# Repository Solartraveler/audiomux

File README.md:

# Audiomux
This project provides a box for switching 4 stereo audio inputs to 4 outputs. Any combination of inputs to outputs can be selected at the same time.
Signal dissortion is minimized by using reed relays.
Moreover, this provides galvanic isolation from the control circuit and if the input source can drive a headphone, it will work on the output of the mux too.
Allowing control by two USB ports, this can be easily used for a homeoffice + private PC setup. Controlling with an infrared remote control is possible too.
The power supply can come from one of the USB ports or one of two external 6-12V power supplies.
For each power supply source, one predefined input to output mux configuration can be saved in the internal flash.

## Host program
A host program for communicating is provided.
Written in python, it is platform independent. Linux was tested.
Setting output 1 to input 2, call the program as following:

./audiomux-control.py 1 2

Call without parameters to get the current setup. Call

./audiomux-control.py state

to get all predefined configurations for IR remote control codes and Vcc inputs.
The input voltages and internal temperature are printed too.

A debian package can be generated.

## Compiling and uploading

There is no additional programming hardware needed.

With apt install the packages gcc-arm-none-eabi, make, dfu-util and python3-usb.

Next, call make

Then close J4 and call ./dfu-upload.sh

Later, leave J4 open to directly start the flashed program. You have to repeat this for both PCBs.

## Debugging

You can add a serial port with 3.3V level to J11 and see some debug messages when using 19200baud.

Debugging with SWD should be possible too, but this was not tested.

## Bugs

Maybe the biggest bug in the is the counterintuitive ordering of the in and outputs...

The soldering bridges would allow switching input (3 and 4) and/or (1 and 2).

## Libraries used and licenses

The software uses several open source libraries with different licenses.

The HAL library from ST is published under the BSD 3-Clause license.

Some CMSIS header files are published under the Apache 2.0 license.

The [IRMP](https://www.mikrocontroller.net/articles/IRMP_-_english) project is published under GPL 2.0 or later.

[Libusb_stm32](https://github.com/dmitrystu/libusb_stm32) is published under the Apache 2.0 license.

Since GPL 2.0 and Apache 2.0 are considered [incompatible](https://www.apache.org/licenses/GPL-compatibility.html) by the Free Software Foundation, but GPL 3.0 is considered compatible, GPL 3.0 is the only possible license for the firmware on the microcontroller side.

The PCB is under creative common license. [CC-BY-SA 3.0 DE](https://creativecommons.org/licenses/by-sa/3.0/de/deed.en)

## Windows users

The device declares itself als WCID compatible and uses WinUSB.
So no driver installation is required.
You still need libusb-1.0.dll either in your system directory or in the same directory as the audiomux-control.py script.
The lib can be found [here](https://libusb.info). Tested with version 1.0.24, the dll can be found in VS2019\MS64\dll.

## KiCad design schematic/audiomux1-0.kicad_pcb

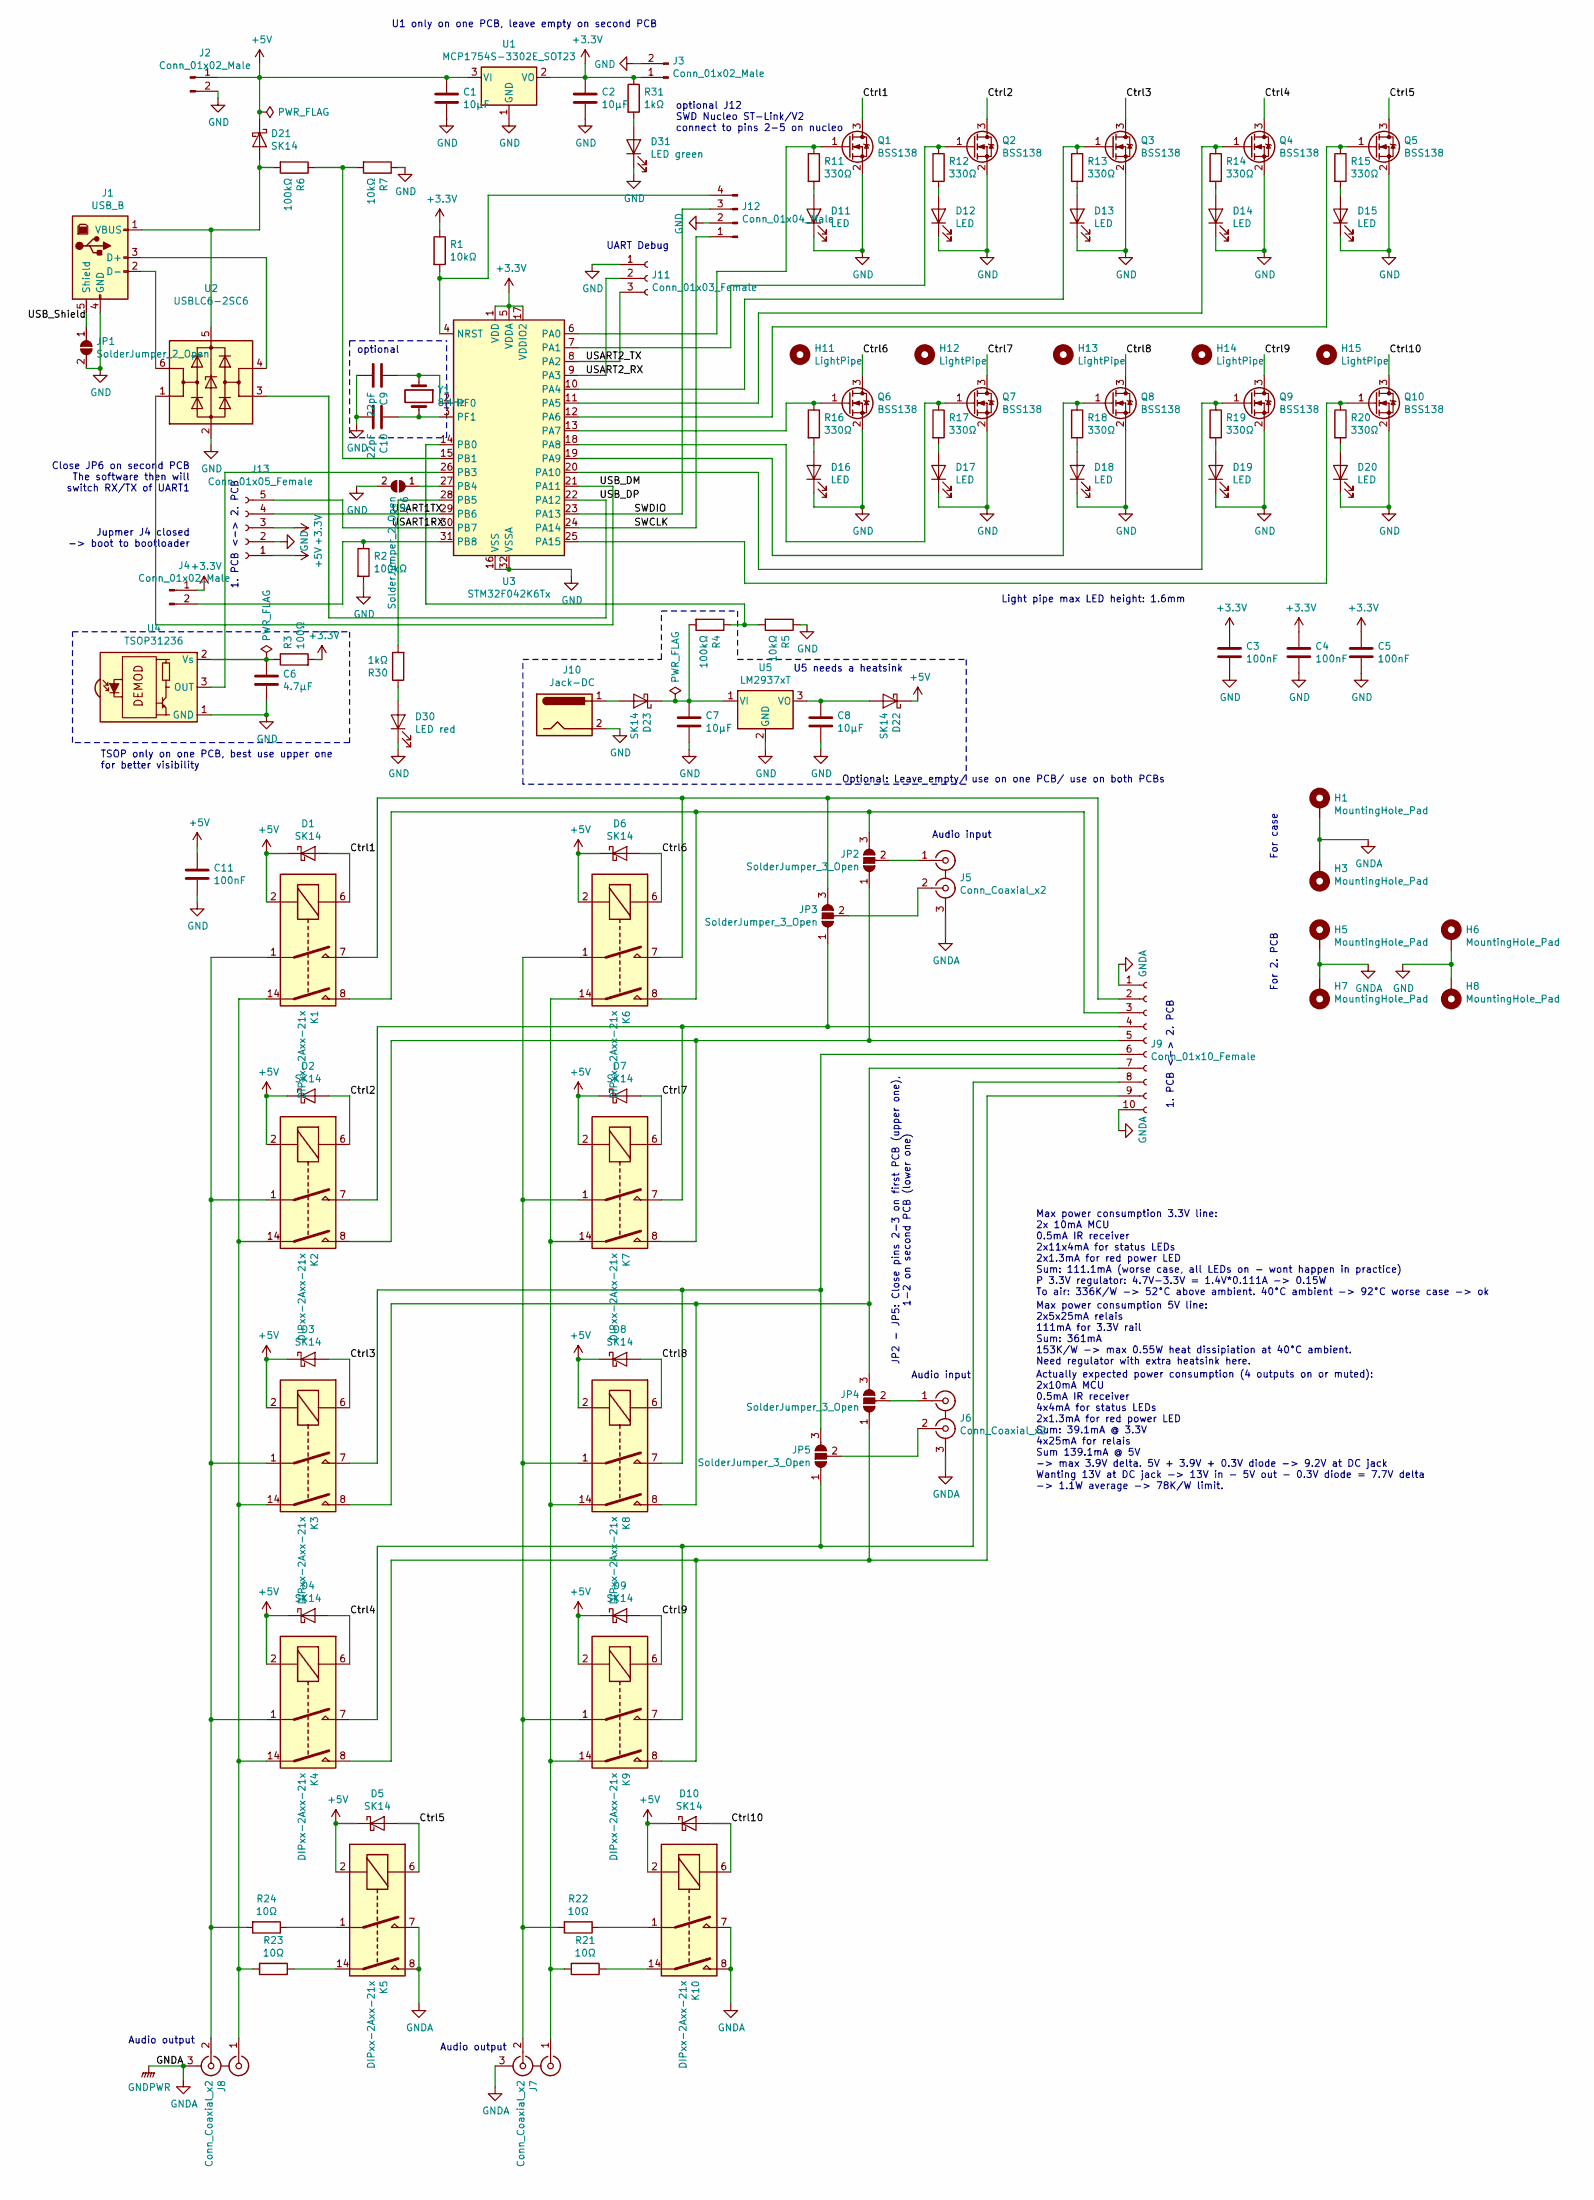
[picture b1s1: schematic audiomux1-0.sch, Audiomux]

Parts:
C1, C2, C8: 10µF; C_0805_2012Metric_Pad1.18x1.45mm_HandSolder
C3, C4, C5, C11: 100nF; C_0805_2012Metric_Pad1.18x1.45mm_HandSolder
C6: 4.7µF; C_0805_2012Metric_Pad1.18x1.45mm_HandSolder
C7: 10µF; C_1206_3216Metric_Pad1.33x1.80mm_HandSolder
C9, C10: 22pF; C_0805_2012Metric_Pad1.18x1.45mm_HandSolder
D1, D2, D3, D4, D5, D6, D7, D8, D9, D10, D21, D22, D23: SK14; D_SMA_Handsoldering
D11, D12, D13, D14, D15, D16, D17, D18, D19, D20: LED; LED_miniPLCC_2315_Handsoldering
D30: LED red; LED_0805_2012Metric_Pad1.15x1.40mm_HandSolder
D31: LED green; LED_0805_2012Metric_Pad1.15x1.40mm_HandSolder
H1, H3: MountingHole_Pad; MountingHole_2.7mm_M2.5_DIN965_Pad
H5, H6, H7, H8: MountingHole_Pad; MountingHole_3.2mm_M3_DIN965_Pad
H11, H12, H13, H14, H15: LightPipe; Lightpipe_LPF-C012303S
J1: USB_B; USB_B_OST_USB-B1HSxx_Horizontal
J2, J3: Conn_01x02_Male; TestPoint_2Pads_Pitch2.54mm_Drill0.8mm
J4: Conn_01x02_Male; PinHeader_1x02_P2.54mm_Vertical
J5, J6, J7, J8: Conn_Coaxial_x2; CBP2
J9: Conn_01x10_Female; PinSocket_1x10_P2.54mm_Vertical
J10: Jack-DC; BarrelJack_Horizontal_HEBW21
J11: Conn_01x03_Female; PinSocket_1x03_P2.54mm_Vertical
J12: Conn_01x04_Male; PinHeader_1x04_P2.54mm_Vertical
J13: Conn_01x05_Female; PinSocket_1x05_P2.54mm_Vertical
JP1, JP6: SolderJumper_2_Open; SolderJumper-2_P1.3mm_Open_RoundedPad1.0x1.5mm
JP2, JP3, JP4, JP5: SolderJumper_3_Open; SolderJumper-3_P1.3mm_Open_RoundedPad1.0x1.5mm
K1, K2, K3, K4, K5, K6, K7, K8, K9, K10: DIPxx-2Axx-21x; Relay_StandexMeder_DIP_LowProfile
Q1, Q2, Q3, Q4, Q5, Q6, Q7, Q8, Q9, Q10: BSS138; SOT-23_Handsoldering
R1, R5, R7: 10kΩ; R_0805_2012Metric_Pad1.20x1.40mm_HandSolder
R2, R4, R6: 100kΩ; R_0805_2012Metric_Pad1.20x1.40mm_HandSolder
R3: 100Ω; R_0805_2012Metric_Pad1.20x1.40mm_HandSolder
R11, R12, R13, R14, R15, R16, R17, R18, R19, R20: 330Ω; R_0805_2012Metric_Pad1.20x1.40mm_HandSolder
R21, R22, R23, R24: 10Ω; R_2512_6332Metric_Pad1.40x3.35mm_HandSolder
R30, R31: 1kΩ; R_0805_2012Metric_Pad1.20x1.40mm_HandSolder
U1: MCP1754S-3302E_SOT23; SOT-23_Handsoldering
U2: USBLC6-2SC6; SOT-23-6
U3: STM32F042K6Tx; LQFP-32_7x7mm_P0.8mm
U4: TSOP31236; Vishay_CAST-3Pin
U5: LM2937xT; TO-220-3_Vertical
Y1: 8MHz; Crystal_HC49-U_Vertical

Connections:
+3V3: C2.1, C3.1, C4.1, C5.1, J3.1, J4.1, J13.3, R1.1, R3.2, R31.1, U1.2 (VO), U3.1 (VDD), U3.5 (VDDA), U3.17 (VDDIO2)
+5V: C1.1, C11.1, D1.1 (K), D2.1 (K), D3.1 (K), D4.1 (K), D5.1 (K), D6.1 (K), D7.1 (K), D8.1 (K), D9.1 (K), D10.1 (K), D21.1 (K), D22.1 (K), J2.1, J13.1, K1.2, K2.2, K3.2, K4.2, K5.2, K6.2, K7.2, K8.2, K9.2, K10.2, U1.3 (VI)
/Ctrl1: D1.2 (A), K1.6, Q1.3 (D)
/Ctrl2: D2.2 (A), K2.6, Q2.3 (D)
/Ctrl3: D3.2 (A), K3.6, Q3.3 (D)
/Ctrl4: D4.2 (A), K4.6, Q4.3 (D)
/Ctrl5: D5.2 (A), K5.6, Q5.3 (D)
/Ctrl6: D6.2 (A), K6.6, Q6.3 (D)
/Ctrl7: D7.2 (A), K7.6, Q7.3 (D)
/Ctrl8: D8.2 (A), K8.6, Q8.3 (D)
/Ctrl9: D9.2 (A), K9.6, Q9.3 (D)
/Ctrl10: D10.2 (A), K10.6, Q10.3 (D)
/SWCLK: J12.1, U3.24 (PA14)
/SWDIO: J12.3, U3.23 (PA13)
/USART1RX: J13.5, U3.30 (PB7)
/USART1TX: J13.4, U3.29 (PB6)
/USART2_RX: J11.2, U3.9 (PA3)
/USART2_TX: J11.3, U3.8 (PA2)
/USB_DM: U2.1 (I/O1), U3.21 (PA11)
/USB_DP: U2.3 (I/O2), U3.22 (PA12)
/USB_Shield: J1.5 (Shield), JP1.1 (A)
GND: C1.2, C2.2, C3.2, C4.2, C5.2, C6.2, C7.2, C8.2, C9.2, C10.2, C11.2, D11.1 (K), D12.1 (K), D13.1 (K), D14.1 (K), D15.1 (K), D16.1 (K), D17.1 (K), D18.1 (K), D19.1 (K), D20.1 (K), D30.1 (K), D31.1 (K), H6.1, H8.1, J1.4 (GND), J2.2, J3.2, J10.2, J11.1, J12.2, J13.2, JP1.2 (B), JP6.2 (B), Q1.2 (S), Q2.2 (S), Q3.2 (S), Q4.2 (S), Q5.2 (S), Q6.2 (S), Q7.2 (S), Q8.2 (S), Q9.2 (S), Q10.2 (S), R2.2, R5.1, R7.1, U1.1 (GND), U2.2 (GND), U3.16 (VSS), U3.32 (VSSA), U4.1 (GND), U5.2 (GND)
GNDA: H1.1, H3.1, H5.1, H7.1, J5.3 (EXT), J6.3 (EXT), J7.3 (EXT), J8.3 (EXT), J9.1, J9.10, K5.7, K5.8, K10.7, K10.8
unnamed: C6.1, R3.1, U4.2 (Vs)
unnamed: C7.1, D23.1 (K), R4.2, U5.1 (VI)
unnamed: C8.1, D22.2 (A), U5.3 (VO)
unnamed: C9.1, U3.2 (PF0), Y1.1
unnamed: C10.1, U3.3 (PF1), Y1.2
unnamed: D11.2 (A), R11.2
unnamed: D12.2 (A), R12.2
unnamed: D13.2 (A), R13.2
unnamed: D14.2 (A), R14.2
unnamed: D15.2 (A), R15.2
unnamed: D16.2 (A), R16.2
unnamed: D17.2 (A), R17.2
unnamed: D18.2 (A), R18.2
unnamed: D19.2 (A), R19.2
unnamed: D20.2 (A), R20.2
unnamed: D21.2 (A), J1.1 (VBUS), R6.2, U2.5 (VBUS)
unnamed: D23.2 (A), J10.1
unnamed: D30.2 (A), R30.1
unnamed: D31.2 (A), R31.2
unnamed: J1.2 (D-), U2.6 (I/O1)
unnamed: J1.3 (D+), U2.4 (I/O2)
unnamed: J4.2, R2.1, U3.31 (PB8)
unnamed: J5.1 (IN1), JP2.2 (C)
unnamed: J5.2 (IN2), JP3.2 (C)
unnamed: J6.1 (IN1), JP4.2 (C)
unnamed: J6.2 (IN2), JP5.2 (C)
unnamed: J7.1 (IN1), K6.14, K7.14, K8.14, K9.14, R21.2
unnamed: J7.2 (IN2), K6.1, K7.1, K8.1, K9.1, R22.2
unnamed: J8.1 (IN1), K1.14, K2.14, K3.14, K4.14, R23.2
unnamed: J8.2 (IN2), K1.1, K2.1, K3.1, K4.1, R24.2
unnamed: J9.2, JP3.3 (B), K1.7, K6.7
unnamed: J9.3, JP2.3 (B), K1.8, K6.8
unnamed: J9.4, JP3.1 (A), K2.7, K7.7
unnamed: J9.5, JP2.1 (A), K2.8, K7.8
unnamed: J9.6, JP5.3 (B), K3.7, K8.7
unnamed: J9.7, JP4.3 (B), K3.8, K8.8
unnamed: J9.8, JP5.1 (A), K4.7, K9.7
unnamed: J9.9, JP4.1 (A), K4.8, K9.8
unnamed: J12.4, R1.2, U3.4 (NRST)
unnamed: JP6.1 (A), U3.27 (PB4)
unnamed: K5.1, R24.1
unnamed: K5.14, R23.1
unnamed: K10.1, R22.1
unnamed: K10.14, R21.1
unnamed: Q1.1 (G), R11.1, U3.6 (PA0)
unnamed: Q2.1 (G), R12.1, U3.7 (PA1)
unnamed: Q3.1 (G), R13.1, U3.10 (PA4)
unnamed: Q4.1 (G), R14.1, U3.11 (PA5)
unnamed: Q5.1 (G), R15.1, U3.12 (PA6)
unnamed: Q6.1 (G), R16.1, U3.13 (PA7)
unnamed: Q7.1 (G), R17.1, U3.18 (PA8)
unnamed: Q8.1 (G), R18.1, U3.19 (PA9)
unnamed: Q9.1 (G), R19.1, U3.20 (PA10)
unnamed: Q10.1 (G), R20.1, U3.25 (PA15)
unnamed: R4.1, R5.2, U3.14 (PB0)
unnamed: R6.1, R7.2, U3.15 (PB1)
unnamed: R30.2, U3.28 (PB5)
unnamed: U3.26 (PB3), U4.3 (OUT)

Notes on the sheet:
Jupmer J4 closed -> boot to bootloader
U1 only on one PCB, leave empty on second PCB
optional J12 SWD Nucleo ST-Link/V2 connect to pins 2-5 on nucleo
UART Debug
Max power consumption 3.3V line: 2x 10mA MCU 0.5mA IR receiver 2x11x4mA for status LEDs 2x1.3mA for red power LED Sum: 111.1mA (worse case, all LEDs on - wont happen in practice) P 3.3V regulator: 4.7V-3.3V = 1.4V*0.111A -> 0.15W To air: 336K/W -> 52°C above ambient. 40°C ambient -> 92°C worse case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
Max power consumption 5V line: 2x5x25mA relais 111mA for 3.3V rail Sum: 361mA 153K/W -> max 0.55W heat dissipiation at 40°C ambient. Need regulator with extra heatsink here.
Actually expected power consumption (4 outputs on or muted): 2x10mA MCU 0.5mA IR receiver 4x4mA for status LEDs 2x1.3mA for red power LED Sum: 39.1mA @ 3.3V 4x25mA for relais Sum 139.1mA @ 5V -> max 3.9V delta. 5V + 3.9V + 0.3V diode -> 9.2V at DC jack Wanting 13V at DC jack -> 13V in - 5V out - 0.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
Close JP6 on second PCB The software then will switch RX/TX of UART1
Optional: Leave empty/ use on one PCB/ use on both PCBs
U5 needs a heatsink
JP2 - JP5: Close pins 2-3 on first PCB (upper one), 1-2 on second PCB (lower one)
For case
For 2. PCB
optional
Light pipe max LED height: 1.6mm
Audio input
Audio output
1. PCB <-> 2. PCB
TSOP only on one PCB, best use upper one for better visibility

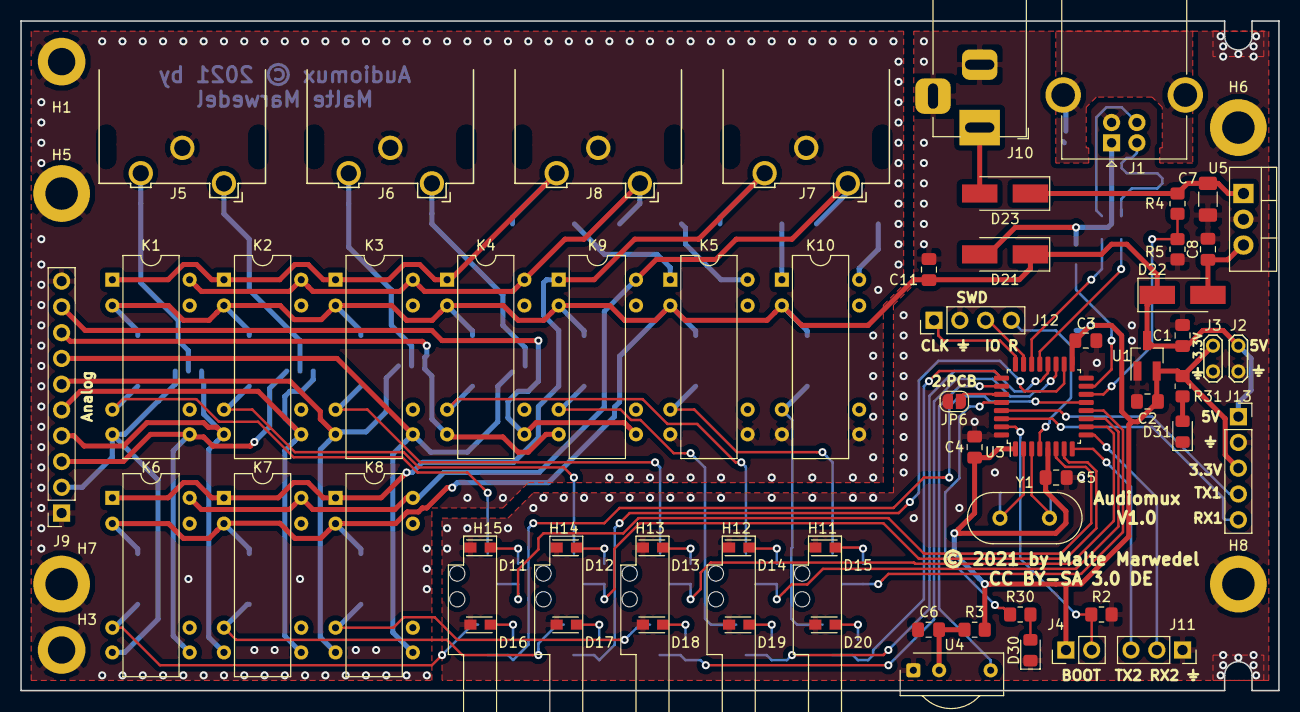
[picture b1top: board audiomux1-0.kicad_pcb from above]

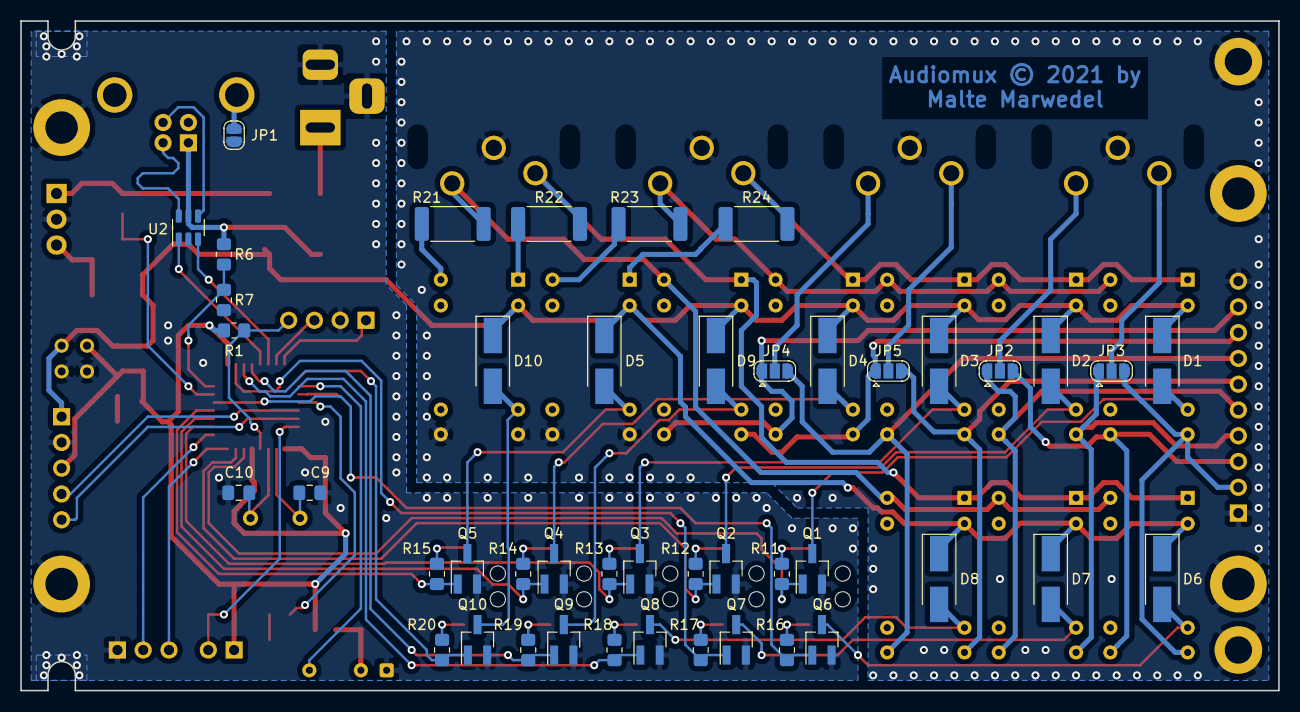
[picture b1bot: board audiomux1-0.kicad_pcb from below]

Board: 2 copper layers, 124.0 x 66.0 mm, 115 parts (45 on the bottom side), 81 nets.

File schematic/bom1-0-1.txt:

To get the right enumeration of inputs and outputs, place the 1.PCB on top of the 2.PCB.
Then the enumeration of the backside will look linke the following:
Output1 Output2 Input1 Input2 <- 1.PCB
Output3 Output4 Input3 Input4 <- 2.PCB
I reccommend solder the 2.PCB first - then adjusting the height of J9 and J13 headers is easier when the spacers are in place.
U1 may only be present on one PCB. It does not matter which one - but I suggest the one you solder first.


1. and 2. PCB - duplicate number of parts to order
                     Description              Ordner number of reichelt.de
C1, C2               10µF, 16V 0805           X5R-G0805 10/16
C3, C4, C5, C11      100nF 0805               X7R-G0805 100N
D1-D10, D23          Schottky diode SK14      SK 14 DIO
D11-D14, D16-D19     LED yellow PLCC2         LED SMD 2214 GE
D15, D20             LED red    PLCC2         LED SMD 2214 RT
D30                  LED red 0805             OSO LSR976
D31                  LED green 0805           OSO LGR971
H11-H15              dual light pipe          DIAL 515-1094F
J1                   USB B jack               USB BW
J4                   2pin 2.54mm header       MPE 087-1-002
J5-J8                Stereo cinch connector   CBP 2
J11                  3pin socket 2.54mm Debug MPE 094-1-003
K1-K10               Reed relai 2x on         LITT HE722A0500
Q1-Q10               BSS138 N channel mosfet  BSS 138 SMD
R1, R5, R7           10k 0805                 SMD-0805 10,0K
R2, R6               100k 0805                SMD-0805 100K
R11-R20              330 0805                 SMD-0805 330
R21-R24              10 1W 2512               RND 1552512 AA
R30, R31             1k 0805                  SMD-0805 1,00K
U2                   USB esd protection       USBLC6-2SC6
U3                   STM32F042K6T             ---

1.PCB (top):
Jumper for J4        Share with 2. PCB
J9                   10pin long header 2.54mm MPE 089-1-010
J13                  5pin long header 2.54mm  MPE 089-1-005

2.PCB (bottom):
U1                   3.3V regulator, MCP1754S CP 1754-3302CB
J9                   10pin socket 2.54mm      MPE 094-1-010
J13                  5pin socket 2.54mm       MPE 094-1-005

Between 1.PCB and 2.PCB
-- 4x                Spacer 3mm 30mm height   DA 30MM
-- 4x                Screw 3mm                --
-- 4x                Screw-nut 3mm            --

Optional for DC jack:
C7                   10µF, 25V 1206           X7R-G1206 10/25
C8                   10µF, 16V 0805           X5R-G0805 10/16
D21, D22             Schottky diode SK14      SK 14 DIO
J10                  DC Jack                  DC BU21 90
R4                   100k 0805                SMD-0805 100K
U5                   5V regulator, min 400mA  LM 2937 ET-5.0
Heatsink for U5:     TO220, <=78K/K           ---

Optional for IR receiver.
Suggestion: Solder only on 2.PCB - its higer and therefore the view
is less likely blocked by other things on a table or elsewhere.
R3                   100 0805                 SMD-0805 100
U4                   IR receiver TSOP31236    TSOP 31236
C6                   4.7µF 0805               KEM X5R0805 4,7U

Optional for crystal:
C9, C10              22pF 0805                NPO-G0805 22P
Y1                   8MHz crystal             8,0000-HC49U-S

Optional for debugging:
J12                  SWD debug 4pin header    MPE 087-1-004

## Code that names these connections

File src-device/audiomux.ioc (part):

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Mcu.UserName=STM32F042K6Tx
PA3.GPIO_PuPd=GPIO_PULLUP
PA0.GPIO_Label=SoundA1
PA9.GPIOParameters=GPIO_Label
PA11.Mode=Device
PA3.GPIOParameters=GPIO_PuPd
PA6.GPIO_Label=SoundAMute
PB0.GPIO_Label=JackVcc
RCC.SYSCLKSource=RCC_SYSCLKSOURCE_HSI48
PB5.GPIOParameters=PinState,GPIO_Label
PA15.GPIO_Label=SoundBMute
PB4.GPIOParameters=GPIO_PuPd,GPIO_Label
PA12.Signal=USB_DP
PF0-OSC_IN.GPIO_PuPd=GPIO_PULLDOWN
PB6.Signal=USART1_TX
PB5.PinState=GPIO_PIN_SET
PB6.Mode=Asynchronous
PA8.GPIOParameters=GPIO_Label
PF0-OSC_IN.GPIO_Label=Crystal0
PB0.GPIOParameters=GPIO_Label
PB3.GPIO_PuPd=GPIO_PULLUP
PA1.GPIOParameters=GPIO_Label
PA14.Mode=Serial_Wire
PB1.GPIO_Label=UsbVcc
PA10.GPIO_Label=SoundB4
PB3.GPIOParameters=GPIO_PuPd,GPIO_Label
PB7.Signal=USART1_RX
PA8.Signal=GPIO_Output
PA0.Signal=GPIO_Output
Mcu.Package=LQFP32
PB1.Signal=SharedAnalog_PB1
PA6.Signal=GPIO_Output
PA10.Signal=GPIO_Output
PA15.Signal=GPIO_Output
PA5.GPIOParameters=GPIO_Label
PB5.GPIO_Label=LED
PA4.GPIO_Label=SoundA3
PF1-OSC_OUT.Signal=GPIO_Input
PB4.Signal=GPIO_Input
PA3.Signal=USART2_RX
PB3.GPIO_Label=IrReceiver
PA6.GPIOParameters=PinState,GPIO_Label
PB8.GPIOParameters=GPIO_PuPd,GPIO_Label
PA15.GPIOParameters=PinState,GPIO_Label
PA9.GPIO_Label=SoundB3
PB8.GPIO_PuPd=GPIO_PULLDOWN
PA6.PinState=GPIO_PIN_SET
PA13.Signal=SYS_SWDIO
PA3.Mode=Asynchronous
PB8.GPIO_Label=Boot
PA8.GPIO_Label=SoundB2
PF1-OSC_OUT.GPIO_PuPd=GPIO_PULLDOWN
PA9.Signal=GPIO_Output
PB4.GPIO_PuPd=GPIO_PULLUP
PF1-OSC_OUT.GPIOParameters=GPIO_PuPd,GPIO_Label
PA1.Signal=GPIO_Output
PA5.Signal=GPIO_Output
board=custom
PA15.PinState=GPIO_PIN_SET
PB4.GPIO_Label=SecondPcb
PA1.GPIO_Label=SoundA2
PF1-OSC_OUT.GPIO_Label=Crystal1
PA10.GPIOParameters=GPIO_Label
PA4.GPIOParameters=GPIO_Label
PA13.Mode=Serial_Wire
Mcu.Name=STM32F042K(4-6)Tx
PA2.Signal=USART2_TX
PB3.Signal=GPIO_Input
PA4.Signal=GPIO_Output
RCC.SYSCLKFreq_VALUE=48000000
PB5.Signal=GPIO_Output
PA7.GPIO_Label=SoundB1
PA12.Mode=Device
PA5.GPIO_Label=SoundA4
PB7.Mode=Asynchronous
PA11.Signal=USB_DM
PA14.Signal=SYS_SWCLK
PA0.GPIOParameters=GPIO_Label
PA2.Mode=Asynchronous
PB8.Signal=GPIO_Input
PF0-OSC_IN.Signal=GPIO_Input
PF0-OSC_IN.GPIOParameters=GPIO_PuPd,GPIO_Label
PB0.Signal=GPIO_Analog
PA7.GPIOParameters=GPIO_Label
PB1.GPIOParameters=GPIO_Label
PA7.Signal=GPIO_Output

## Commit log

2021-02-07 Inital checkin. Schematic and BOM complete. Host program complete. USB communication works. Each MCU can control the own switches. Inter MCU communication not implemented. IR remote control untestd.
2021-02-07 Update documentation. Fix test runner.
2021-02-12 Add inter MCU communication, fix IR receive. Use HSI with PLL for clock, to make sure the inter MCU communication works reliable. Decrease clock from 12 ot 10MHz - minimum for USB. All planned featur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
2021-02-14 Increase inter MCU UART frequency Cleanup code - remove parts of the HAL and replace snprintf with own implementation - much smaller.
2021-02-17 Remove unused HAL files
2021-02-20 Analyze stack usage Add WCID extension to use WinUSB automatically
2021-02-20 Change PID. Add code for generating a debian package.
2021-02-21 Optimize library search path for windows
2021-02-21 Optimize library search path for windows and error messages.
2021-02-22 Replace HAL timer by own implementation. Saves some bytes.
2021-02-24 Add not connected option - output can be disconnected without pulldown now.
2021-02-26 Remove generated control file. Automatically extract package version from python script for .deb file.
2021-04-27 Add CNC files. Show backside of the case
2021-04-27 Fix documentation
2021-04-27 Fix ci script for building debian package

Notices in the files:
schematic/audiomux1-0.kicad_pcb:
CC-BY-SA DE 3.0
Audiomux © 2021 by
Malte Marwedel
© 2021 by Malte Marwedel
CC BY-SA 3.0 DE
